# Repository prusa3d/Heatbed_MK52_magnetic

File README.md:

# Heatbed MK52 magnetic
## KiCad PCB layout

24V rev.05d

12V rev.05e

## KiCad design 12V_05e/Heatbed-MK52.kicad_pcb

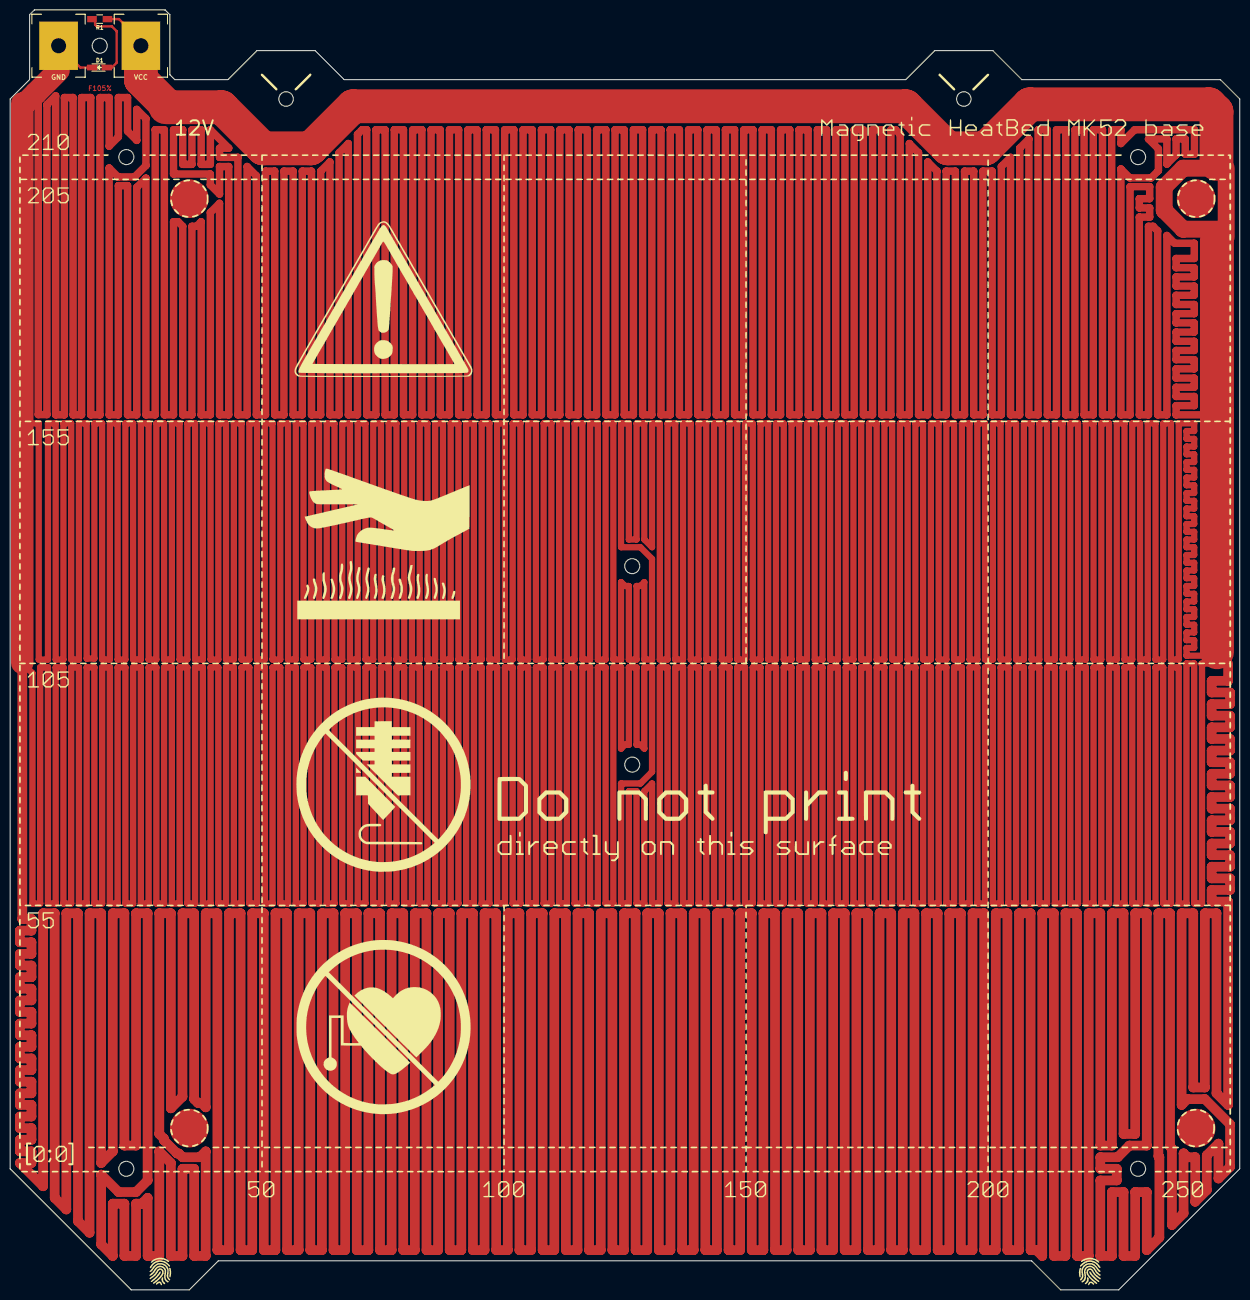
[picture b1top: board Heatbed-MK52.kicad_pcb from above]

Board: 2 copper layers, 254.0 x 264.4 mm, 4 parts (0 on the bottom side), 2 nets.

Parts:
D1: LED_ALT; LED_0805
GND: GND; PCB-Large-pad
R1: 1k; R_0805
VCC: VCC; PCB-Large-pad

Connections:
unnamed: D1.1, GND.1, R1.1, VCC.1
unnamed: D1.2, R1.2

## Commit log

2017-12-04 rev.05
2017-12-04 steel sheet
2017-12-05 slots for magnets
